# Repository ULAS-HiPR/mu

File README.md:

# Mu

Mu is a standalone SiPM/scintillator cosmic-ray detector and flight logger developed alongside the [Ogma avionics stack](https://sean-osullivan.com/projects/ogma/). It is designed to fly as its own black box: battery power in, particle and pressure data logged to onboard flash, then post-flight readout.

> [!CAUTION]
> **Rev 1 assembly corrections:** The `MICROFC-60035-SMT-TR1` SiPM footprint nets are reversed. On an existing Rev 1 PCB, mount U3 180 degrees from the orientation indicated by the footprint's pin-1 marker. This puts SiPM pin 3 (cathode) on PCB pad 1, the filtered HV-bias node, and SiPM pin 1 (anode) on PCB pad 3, the U5 inverting-input node. Pins 2 (fast output) and 4 (no connect) then exchange two unused PCB pads.
>
> The Rev 1 footprint also connects centre pad 5 to AGND. [Onsemi specifies pin 5 as no connect and recommends leaving the paddle unsoldered and floating](https://www.onsemi.com/download/data-sheet/pdf/microc-series-d.pdf). On the working board, a tiny piece of Blu Tack on the PCB beneath pad 5 kept the centre paddle off the board, and the sensor was attached to four small solder balls around the outer pads. A new PCB revision should correct the pin 1/pin 3 net mapping and leave pad 5 floating instead of relying on either assembly workaround.

## Hardware

- 50 x 50 x 20 mm BC-408 plastic scintillator.
- Onsemi MicroFC-60035 6 x 6 mm SiPM biased at about 30 V.
- OPA656/OPA814-class transimpedance readout around a 2.5 V reference.
- STM32F042 controller, W25Q128 external flash, and MS5607 barometer.
- Optional CAN interface; standalone logging does not depend on the Ogma stack.

## Repository

- `mu.kicad_sch`, `power.kicad_sch`, and `mu.kicad_pcb` - KiCad hardware design.
- `fabrication/` - Rev 1 manufacturing outputs.
- `Lib/` - project symbols, footprints, and 3D models.
- `SiPM Test Samples/` - raw oscilloscope samples.

Firmware, the field dashboard, and current flight preparation are on [`mu/f042-bringup`](https://github.com/ULAS-HiPR/mu/tree/mu/f042-bringup).

## Status

Mu has detected and logged real particle pulses on the bench and flew at Mach26, but it did not record a clean in-flight particle run. The reproduced fault is mechanical over-compression of the scintillator/SiPM stack. Packaging and flight validation remain in progress; Mu is not yet flight-proven.

## Manufacturing support

Rev 1 PCB fabrication was sponsored through [EasyEDA Education](https://easyeda.com/education) and manufactured by [JLCPCB](https://jlcpcb.com/). The board was designed in KiCad and imported into EasyEDA Pro for the sponsorship and manufacturing workflow.

## More information

See the [Mu project write-up](https://sean-osullivan.com/projects/mu/) for the detector, bring-up failures, pulse captures, and flight diagnosis.

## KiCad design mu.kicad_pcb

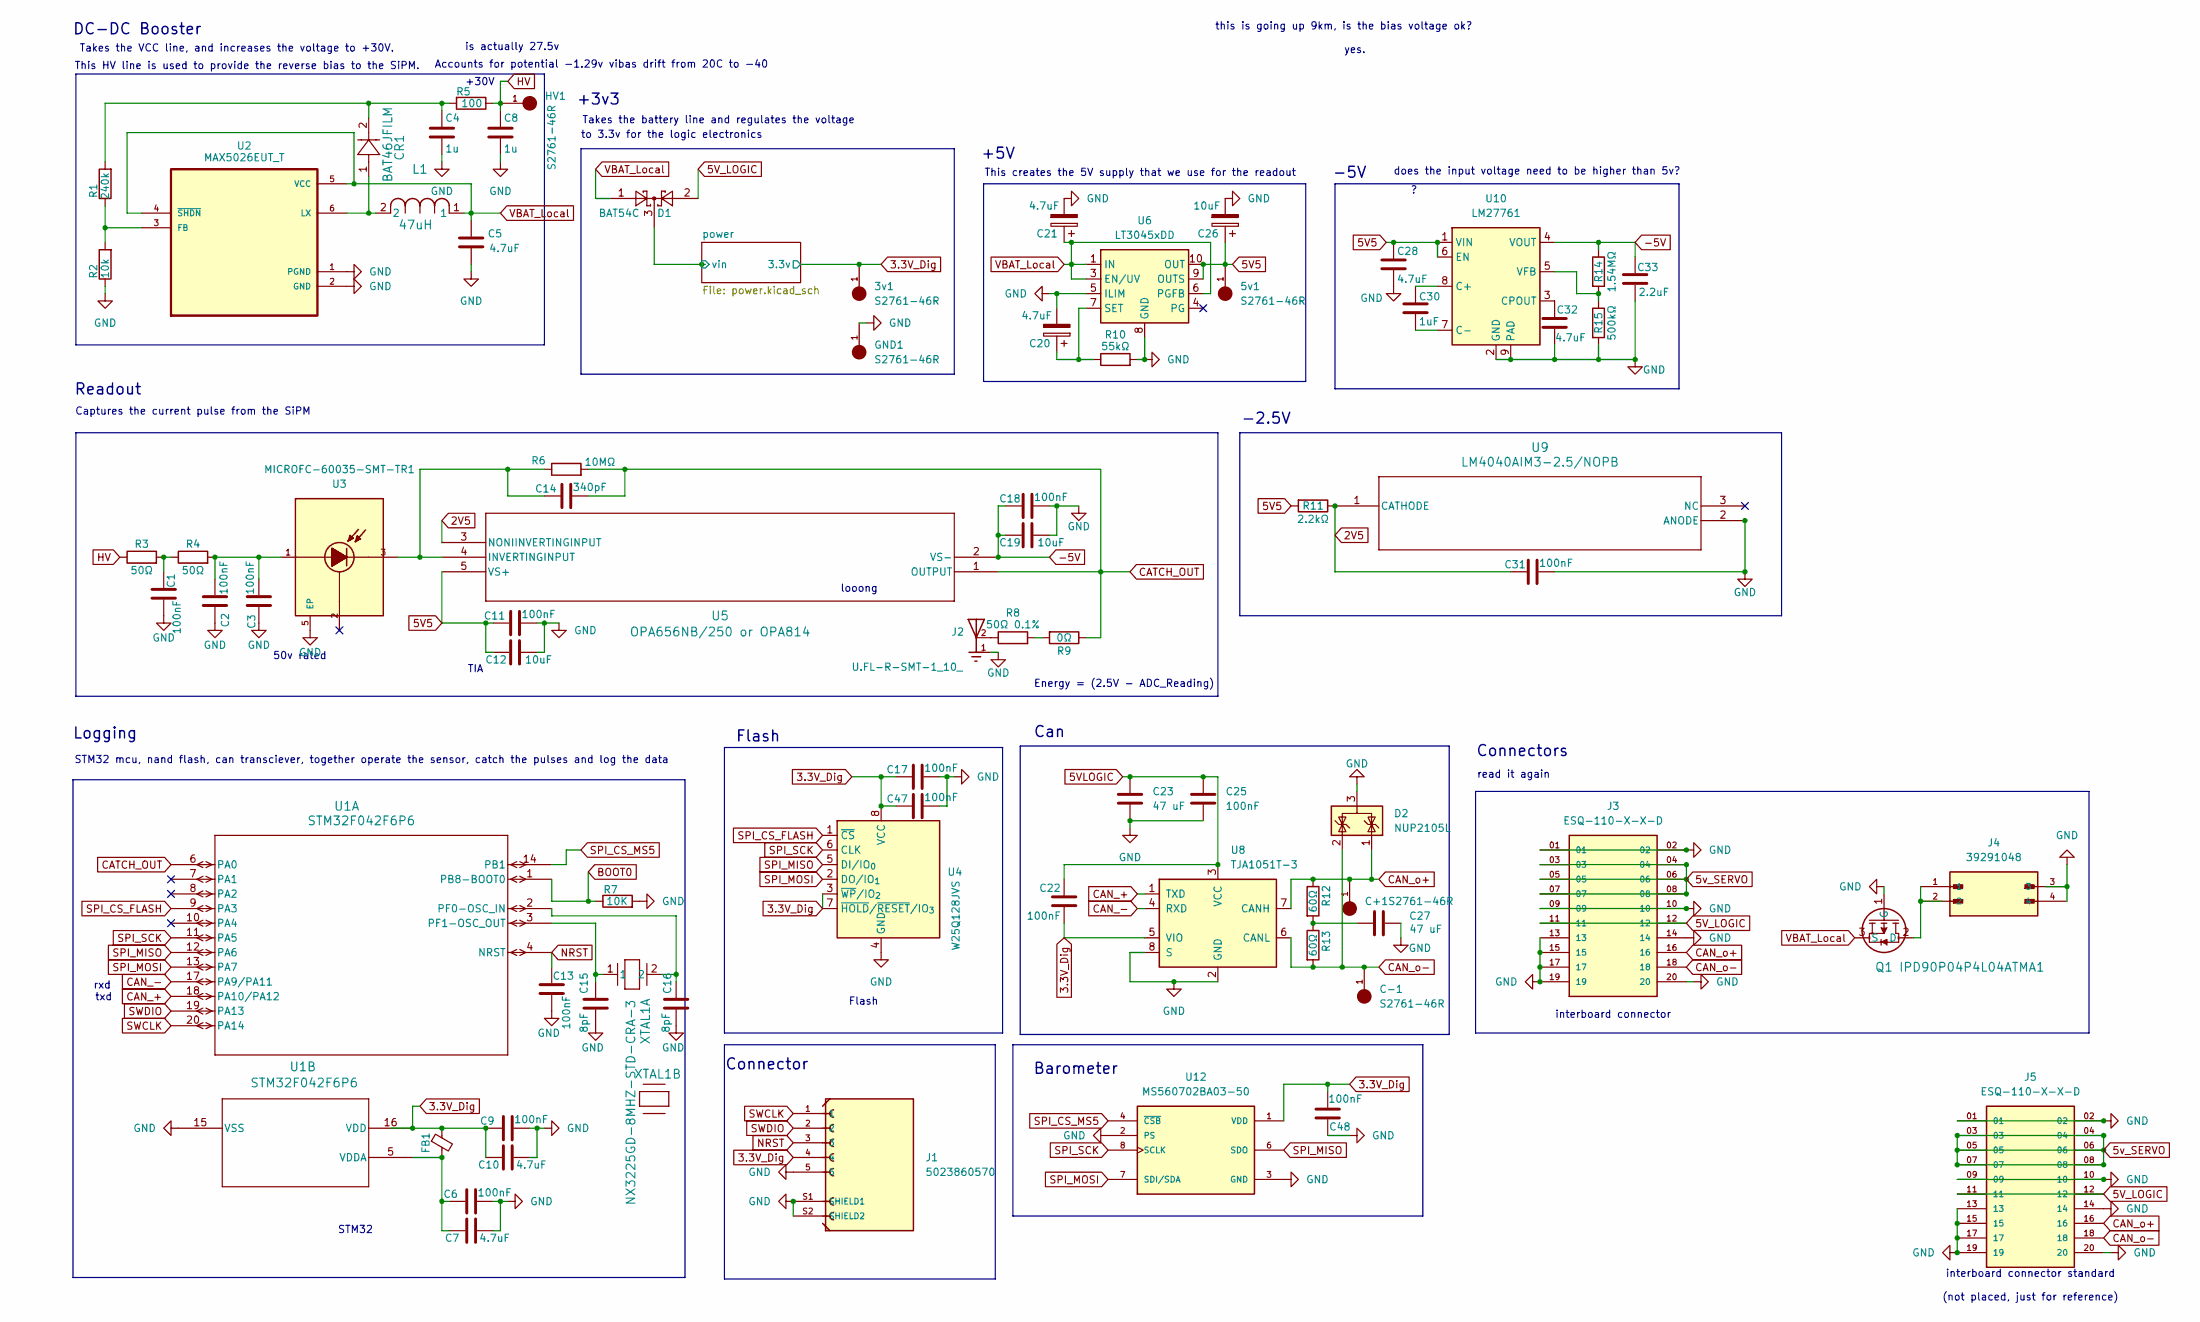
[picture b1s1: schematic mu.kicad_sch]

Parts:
3v1, 5v1: S2761-46R; HARWIN_S2761-46R; PARTREV 1
C1, C2, C3, C6, C9, C11, C13, C17, C18, C22, C25, C31, C47: 100nF; C_0402_1005Metric
C4, C8: 1u; R_0402_1005Metric
C5, C28, C32: 4.7uF; R_0402_1005Metric
C7, C10, C20, C21: 4.7uF; C_0402_1005Metric
C12: 10uF; C_0402_1005Metric
C14: 340pF; C_0402_1005Metric
C15, C16: 8pF; C_0402_1005Metric
C19, C26: 10uF; C_0603_1608Metric
C23, C27: 47 uF; C_0603_1608Metric
C30: 1uF; R_0402_1005Metric
C33: 2.2uF; C_0603_1608Metric
C48: 100nF; R_0402_1005Metric
C+1: S2761-46R; HARWIN_S2761-46R; PARTREV 1
C-1: S2761-46R; HARWIN_S2761-46R; PARTREV 1
CR1: BAT46JFILM; SOD-323_STM
D1: BAT54C; SOT-23
D2: NUP2105L; SOT-23
FB1: ferrite; L_0402_1005Metric
GND1: S2761-46R; HARWIN_S2761-46R; PARTREV 1
HV1: S2761-46R; HARWIN_S2761-46R; PARTREV 1
J1: 5023860570; MOLEX_5023860570; PARTREV F
J2: U.FL-R-SMT-1_10_; HRS_U.FL-R-SMT-1_10_
J3, J5: ESQ-110-X-X-D; SAMTEC_ESQ-110-14-G-D; PARTREV NA
J4: 39291048; MOLEX_39291048; PARTREV N1
L1: 47uH; IND_BOURNS_SRN4018
Q1: IPD90P04P4L04ATMA1; PG-TO252-3-313_INF-L
R1: 240k; R_0402_1005Metric
R2: 10k; R_0402_1005Metric
R3, R4: 50Ω; R_0402_1005Metric
R5: 100; R_0402_1005Metric
R6: 10MΩ; R_0402_1005Metric
R7: 10K; R_0402_1005Metric
R8: 50Ω 0.1%; R_0402_1005Metric
R9: 0Ω; R_0402_1005Metric
R10: 55kΩ; R_0402_1005Metric
R11: 2.2kΩ; R_0402_1005Metric
R12, R13: 60Ω; R_0402_1005Metric
R14: 1.54MΩ; R_0402_1005Metric
R15: 500kΩ; R_0402_1005Metric
U1: STM32F042F6P6; TSSOP20
U2: MAX5026EUT_T; SOT95P280X145-6N
U3: MICROFC-60035-SMT-TR1; XDCR_MICROFC-60035-SMT-TR1; PARTREV 31 JUL 2018
U4: W25Q128JVS; SOIC-8_5.3x5.3mm_P1.27mm
U5: OPA656NB/250 or OPA814; DBV5
U6: LT3045xDD; DFN-10-1EP_3x3mm_P0.5mm_EP1.65x2.38mm
U8: TJA1051T-3; SOIC-8_3.9x4.9mm_P1.27mm
U9: LM4040AIM3-2.5/NOPB; DBZ3
U10: LM27761; WSON-8-1EP_2x2mm_P0.5mm_EP0.9x1.6mm
U12: MS560702BA03-50; SON125P300X500X100-8N
XTAL1: NX3225GD-8MHZ-STD-CRA-3; XTAL_NX3225GD-8MHZ-STD-CRA-3_NDK

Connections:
2V5: C31.1, R11.1, U5.3 (NONIINVERTINGINPUT), U9.1 (CATHODE)
3.3V_Dig: 3v1.1, C9.1, C10.1, C17.1, C22.1, C47.1, C48.2, FB1.1, J1.4, U1.16 (VDD), U4.3 (~WP/IO_{2}), U4.7 (~HOLD/~RESET/IO_{3}), U4.8 (VCC), U8.5 (VIO), U12.1 (VDD); also elsewhere on the board
5V5: 5v1.1, C11.1, C12.1, C26.1, C28.1, R11.2, U5.5 (VS+), U6.9 (OUTS), U6.10 (OUT), U10.1 (VIN), U10.6 (EN); also elsewhere on the board
5VLOGIC: C22.2, C23.1, C25.1, U8.3 (VCC)
5V_LOGIC: D1.2, J3.11, J3.12, J5.11, J5.12
5v_SERVO: J3.03, J3.04, J3.05, J3.06, J3.07, J3.08, J5.03, J5.04, J5.05, J5.06, J5.07, J5.08
-5V: C18.1, C19.1, C33.1, R14.1, U5.2 (VS-), U10.4 (VOUT)
/power/vin: D1.3; also elsewhere on the board
AGND: C1.2, C2.2, C3.1, C4.2, C5.2, C6.2, C7.2, C8.2, C9.2, C10.2, C11.2, C12.2, C13.2, C15.1, C16.2, C17.2, C18.2, C19.2, C20.2, C21.2, C23.2, C25.2, C26.2, C27.2, C28.2, C31.2, C32.2, C33.2, C47.2, C48.1, D2.3 (A), GND1.1, J1.5, J1.S1 (SHIELD1), J1.S2 (SHIELD2), J2.1, J2.3, J3.01, J3.02, J3.09, J3.10, J3.13, J3.14, J3.15, J3.17, J3.19, J3.20, J4.3, J4.4, J5.01, J5.02, J5.09, J5.10, J5.13, J5.14, J5.15, J5.17, J5.19, J5.20, Q1.1 (G), R2.1, R7.2, R10.2, R15.2, U1.15 (VSS), U2.1 (PGND), U2.2 (GND), U3.5 (EP), U4.4 (GND), U6.5 (ILIM), U6.8 (GND), U6.11 (GND), U8.2 (GND), U8.8 (S), U9.2 (ANODE), U10.2 (GND), U10.9 (PAD), U12.2 (PS), U12.3 (GND); also elsewhere on the board
BOOT0: R7.1, U1.1 (PB8-BOOT0)
CAN_+: U1.18 (PA10/PA12), U8.1 (TXD)
CAN_-: U1.17 (PA9/PA11), U8.4 (RXD)
CAN_o+: C+1.1, D2.1 (K), J3.16, J5.16, R12.1, U8.7 (CANH); also elsewhere on the board
CAN_o-: C-1.1, D2.2 (K), J3.18, J5.18, R13.2, U8.6 (CANL); also elsewhere on the board
CATCH_OUT: C14.2, R6.2, R9.1, U1.6 (PA0), U5.1 (OUTPUT)
HV: C8.1, HV1.1, R3.1, R5.1; also elsewhere on the board
NRST: C13.1, J1.3, U1.4 (NRST)
unnamed: C1.1, R3.2, R4.1
unnamed: C2.1, C3.2, R4.2, U3.1
unnamed: C4.1, CR1.2, R1.2, R5.2
unnamed: C27.1, R12.2, R13.1
unnamed: J2.2, R8.1
unnamed: J4.1, J4.2, Q1.2 (D)
unnamed: R8.2, R9.2
unnamed: C16.1, U1.2 (PF0-OSC_IN), XTAL1.2
unnamed: C15.2, U1.3 (PF1-OSC_OUT), XTAL1.1
unnamed: C6.1, C7.1, FB1.2, U1.5 (VDDA)
unnamed: R1.1, R2.2, U2.3 (FB)
unnamed: CR1.1, L1.2, U2.6 (LX)
unnamed: C14.1, R6.1, U3.3, U5.4 (INVERTINGINPUT)
unnamed: C20.1, R10.1, U6.7 (SET)
unnamed: C30.1, U10.8 (C+)
unnamed: C30.2, U10.7 (C-)
unnamed: C32.1, U10.3 (CPOUT)
unnamed: R14.2, R15.1, U10.5 (VFB)
SPI_CS_FLASH: U1.9 (PA3), U4.1 (~CS)
SPI_CS_MS5: U1.14 (PB1), U12.4 (~CSB), U12.5 (~CSB)
SPI_MISO: U1.12 (PA6), U4.5 (DI/IO_{0}), U12.6 (SDO)
SPI_MOSI: U1.13 (PA7), U4.2 (DO/IO_{1}), U12.7 (SDI/SDA)
SPI_SCK: U1.11 (PA5), U4.6 (CLK), U12.8 (SCLK)
SWCLK: J1.1, U1.20 (PA14)
SWDIO: J1.2, U1.19 (PA13)
VBAT_Local: C5.1, C21.1, D1.1, L1.1, Q1.3 (S), U2.4 (~SHDN), U2.5 (VCC), U6.1 (IN), U6.2 (IN), U6.3 (EN/UV), U6.6 (PGFB)

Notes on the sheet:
Takes the battery line and regulates the voltage
looong
rxd
read it again
txd
TIA
Barometer
-5V
interboard connector
DC-DC Booster
-2.5V
Flash
does the input voltage need to be higher than 5v?
interboard connector standard (not placed, just for reference)
STM32 mcu, nand flash, can transciever, together operate the sensor, catch the pulses and log the data
Logging
50v rated
Flash
+3v3
this is going up 9km, is the bias voltage ok? yes.
Readout
This HV line is used to provide the reverse bias to the SiPM.
Takes the VCC line, and increases the voltage to +30V.
This creates the 5V supply that we use for the readout
Connector
is actually 27.5v
Can
+5V
to 3.3v for the logic electronics
Captures the current pulse from the SiPM
Accounts for potential -1.29v vibas drift from 20C to -40
+30V
Connectors
Energy = (2.5V - ADC_Reading)
STM32

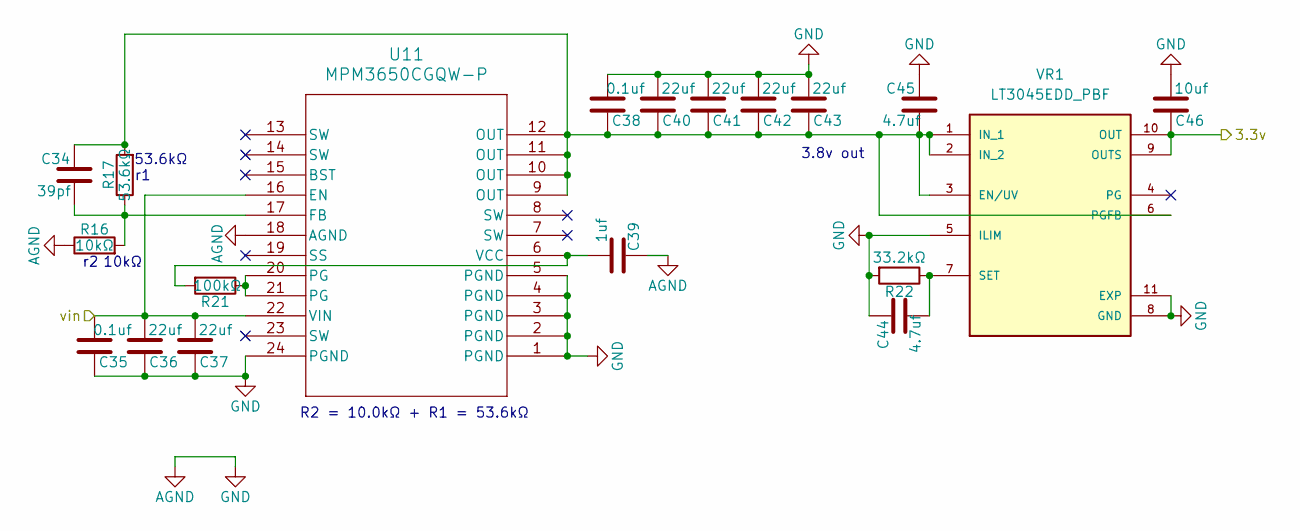
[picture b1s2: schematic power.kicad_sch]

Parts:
C34: 39pf; C_0402_1005Metric
C35, C38: 0.1uf; C_0402_1005Metric
C36, C37, C40, C41, C42, C43: 22uf; C_0603_1608Metric
C39: 1uf; C_0402_1005Metric
C44, C45: 4.7uf; C_0402_1005Metric
C46: 10uf; C_0603_1608Metric
R16: 10kΩ; R_0402_1005Metric
R17: 53.6kΩ; R_0402_1005Metric
R21: 100kΩ; R_0402_1005Metric
R22: 33.2kΩ; R_0402_1005Metric
U11: MPM3650CGQW-P; QFN-24_MPM3650_MNP
VR1: LT3045EDD_PBF; SON50P300X300X80-11N; PARTREV C

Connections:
3.3V_Dig: C46.1, VR1.9 (OUTS), VR1.10 (OUT); also elsewhere on the board
/power/vin: C35.2, C36.2, C37.2, U11.16 (EN), U11.22 (VIN); also elsewhere on the board
AGND: C35.1, C36.1, C37.1, C38.2, C39.1, C40.2, C41.2, C42.2, C43.2, C44.1, C45.1, C46.2, R16.1, R22.2, U11.1 (PGND), U11.2 (PGND), U11.3 (PGND), U11.4 (PGND), U11.5 (PGND), U11.18 (AGND), U11.24 (PGND), VR1.5 (ILIM), VR1.8 (GND), VR1.11 (EXP); also elsewhere on the board
unnamed: R21.1, U11.20 (PG), U11.21 (PG)
unnamed: C34.2, R16.2, R17.1, U11.17 (FB)
unnamed: C39.2, R21.2, U11.6 (VCC)
unnamed: C34.1, C38.1, C40.1, C41.1, C42.1, C43.1, C45.2, R17.2, U11.9 (OUT), U11.10 (OUT), U11.11 (OUT), U11.12 (OUT), VR1.1 (IN_1), VR1.2 (IN_2), VR1.3 (EN/UV), VR1.6 (PGFB)
unnamed: C44.2, R22.1, VR1.7 (SET)

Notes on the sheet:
10kΩ
53.6kΩ
R2 = 10.0kΩ + R1 = 53.6kΩ
3.8v out

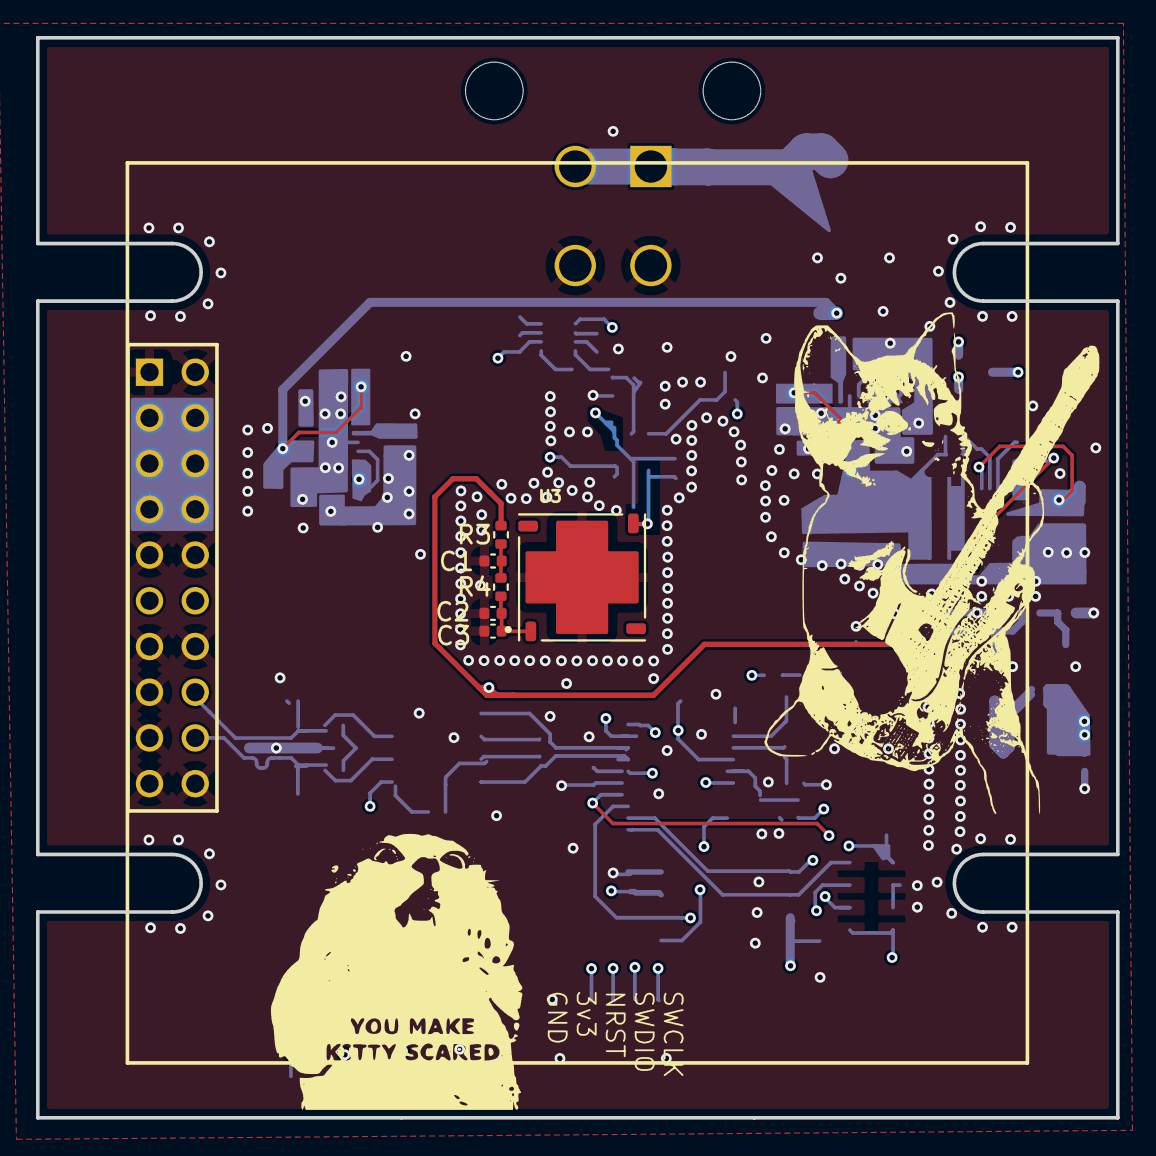
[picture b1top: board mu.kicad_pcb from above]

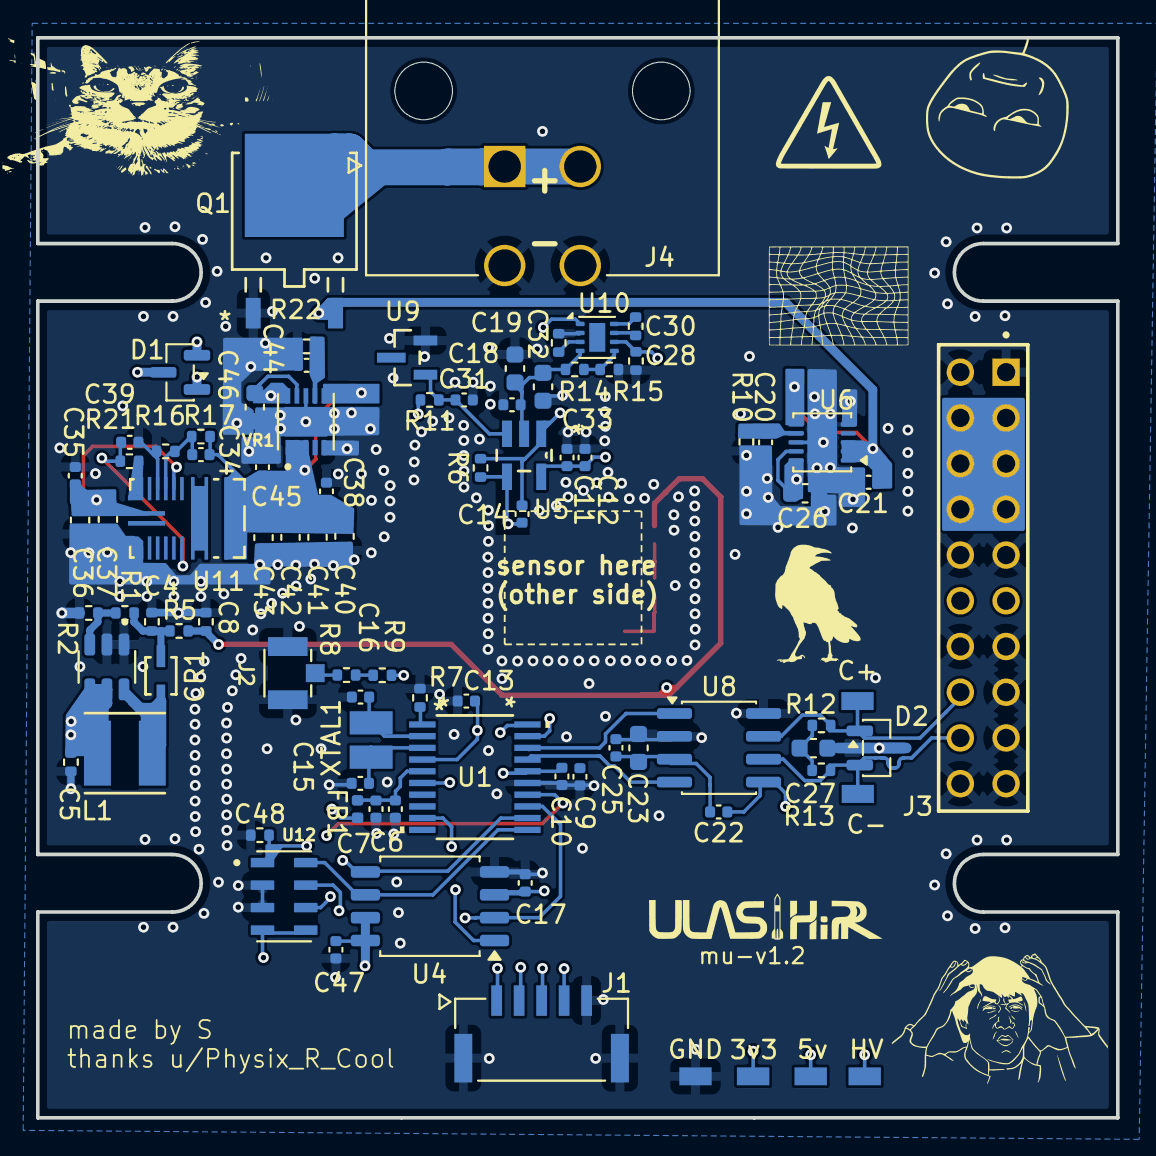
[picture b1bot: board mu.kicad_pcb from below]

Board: 6 copper layers, 60.0 x 60.0 mm, 94 parts (88 on the bottom side), 48 nets.

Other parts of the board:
3v3, 5v: S2761-46R; HARWIN_S2761-46R
C+: S2761-46R; HARWIN_S2761-46R
C-: S2761-46R; HARWIN_S2761-46R
GND: S2761-46R; HARWIN_S2761-46R
HV: S2761-46R; HARWIN_S2761-46R

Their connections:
3.3V_Dig: 3v3.1; also elsewhere on the board
5V5: 5v.1; also elsewhere on the board
AGND: GND.1; also elsewhere on the board
CAN_o+: C+.1; also elsewhere on the board
CAN_o-: C-.1; also elsewhere on the board
HV: HV.1; also elsewhere on the board

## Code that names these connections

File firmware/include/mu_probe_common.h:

#ifndef MU_PROBE_COMMON_H
#define MU_PROBE_COMMON_H

#include "stm32f0xx.h"

#include <cstdint>

namespace mu {

constexpr std::uint32_t kSystemClockHz = 48000000UL;
constexpr std::uint32_t kTimerTickHz = 1000000UL;

constexpr std::uint8_t kCatchOutAdcIndex = 0U;  // PA0
constexpr std::uint8_t kFlashCsIndex = 3U;      // PA3
constexpr std::uint8_t kSpiSckIndex = 5U;       // PA5
constexpr std::uint8_t kSpiMisoIndex = 6U;      // PA6
constexpr std::uint8_t kSpiMosiIndex = 7U;      // PA7
constexpr std::uint8_t kCanRxIndex = 11U;       // PA11
constexpr std::uint8_t kCanTxIndex = 12U;       // PA12
constexpr std::uint8_t kMs5607CsIndex = 1U;     // PB1

constexpr std::uint16_t kCatchOutAdcPin = 1U << kCatchOutAdcIndex;
constexpr std::uint16_t kFlashCsPin = 1U << kFlashCsIndex;
constexpr std::uint16_t kSpiSckPin = 1U << kSpiSckIndex;
constexpr std::uint16_t kSpiMisoPin = 1U << kSpiMisoIndex;
constexpr std::uint16_t kSpiMosiPin = 1U << kSpiMosiIndex;
constexpr std::uint16_t kCanRxPin = 1U << kCanRxIndex;
constexpr std::uint16_t kCanTxPin = 1U << kCanTxIndex;
constexpr std::uint16_t kMs5607CsPin = 1U << kMs5607CsIndex;

enum class SpiWireMode : std::uint8_t {
    Normal = 0U,   // MCU PA7 -> peripheral SDI, peripheral SDO -> MCU PA6.
    Swapped = 1U,  // MCU PA6 -> peripheral DI, peripheral DO -> MCU PA7.
};

enum class SpiClockMode : std::uint8_t {
    Mode0 = 0U,
    Mode3 = 3U,
};

inline void enable_gpio_clocks()
{
    RCC->AHBENR |= RCC_AHBENR_GPIOAEN | RCC_AHBENR_GPIOBEN;
    (void)RCC->AHBENR;
}

inline void set_pin_high(GPIO_TypeDef* port, std::uint16_t pin)
{
    port->BSRR = pin;
}

inline void set_pin_low(GPIO_TypeDef* port, std::uint16_t pin)
{
    port->BRR = pin;
}

inline void configure_input(GPIO_TypeDef* port, std::uint8_t index)
{
    const std::uint32_t shift = static_cast<std::uint32_t>(index) * 2UL;
    port->MODER &= ~(3UL << shift);
    port->PUPDR &= ~(3UL << shift);
}

inline void configure_output(GPIO_TypeDef* port, std::uint8_t index)
{
    const std::uint32_t shift = static_cast<std::uint32_t>(index) * 2UL;
    port->MODER = (port->MODER & ~(3UL << shift)) | (1UL << shift);
    port->OTYPER &= ~(1UL << index);
    port->PUPDR &= ~(3UL << shift);
    port->OSPEEDR |= (3UL << shift);
}

inline void configure_analog(GPIO_TypeDef* port, std::uint8_t index)
{
    const std::uint32_t shift = static_cast<std::uint32_t>(index) * 2UL;
    port->MODER |= (3UL << shift);
    port->PUPDR &= ~(3UL << shift);
}

inline void configure_alternate(GPIO_TypeDef* port, std::uint8_t index, std::uint8_t af)
{
    const std::uint32_t shift = static_cast<std::uint32_t>(index) * 2UL;
    port->MODER = (port->MODER & ~(3UL << shift)) | (2UL << shift);
    port->OTYPER &= ~(1UL << index);
    port->PUPDR &= ~(3UL << shift);
    port->OSPEEDR |= (3UL << shift);

    const std::uint8_t afr_index = index < 8U ? 0U : 1U;
    const std::uint8_t afr_shift = static_cast<std::uint8_t>((index & 7U) * 4U);
    port->AFR[afr_index] =
        (port->AFR[afr_index] & ~(0xFUL << afr_shift)) |
        (static_cast<std::uint32_t>(af) << afr_shift);
}

inline void clock_init_hsi48()
{
    RCC->CR2 |= RCC_CR2_HSI48ON;
    while ((RCC->CR2 & RCC_CR2_HSI48RDY) == 0U) {}

    FLASH->ACR |= FLASH_ACR_LATENCY;

    RCC->CFGR &= ~RCC_CFGR_SW;
    RCC->CFGR |= RCC_CFGR_SW_HSI48;
    while ((RCC->CFGR & RCC_CFGR_SWS) != RCC_CFGR_SWS_HSI48) {}

    SystemCoreClock = kSystemClockHz;
}

inline void systick_init_1khz()
{
    SysTick_Config(kSystemClockHz / 1000UL);
    NVIC_SetPriority(SysTick_IRQn, 0U);
}

inline void timebase_init()
{
    RCC->APB1ENR |= RCC_APB1ENR_TIM3EN;
    (void)RCC->APB1ENR;

    TIM3->PSC = (kSystemClockHz / kTimerTickHz) - 1UL;
    TIM3->ARR = 0xFFFFU;
    TIM3->EGR = TIM_EGR_UG;
    TIM3->CR1 = TIM_CR1_CEN;
}

inline void delay_us(std::uint32_t us)
{
    while (us > 0U) {
        const std::uint32_t chunk = us > 60000U ? 60000U : us;
        TIM3->CNT = 0U;
        while (TIM3->CNT < chunk) {}
        us -= chunk;
    }
}

inline void delay_ms(std::uint32_t ms)
{
    while (ms-- > 0U) {
        delay_us(1000U);
    }
}

inline void configure_safe_chip_selects()
{
    enable_gpio_clocks();
    configure_output(GPIOA, kFlashCsIndex);
    configure_output(GPIOB, kMs5607CsIndex);
    set_pin_high(GPIOA, kFlashCsPin);
    set_pin_high(GPIOB, kMs5607CsPin);
}

} // namespace mu

#endif // MU_PROBE_COMMON_H

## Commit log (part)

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2025-12-14 first
2025-12-14 imported first component
2025-12-14 progress
2025-12-17 big progress, superfluous caps added
2025-12-17 sent v1 to stephen
2025-12-17 push before fabien
2025-12-24 huge progress, caught issue
2025-12-24 clean
2025-12-25 nearly ready for layout
2025-12-26 svgs for readmes
2025-12-28 added usb c and fixed many silly issues
2025-12-28 flipflop is 3v3
2025-12-28 esd protection
2025-12-28 schematic locked in, connenctors added
2025-12-29 ready to place
2026-01-06 layout rocking
2026-01-11 organised
2026-01-12 progress2
2026-01-12 progress3
2026-01-14 nearly done now
2026-01-15 restructuring now that we've got the standard connector
2026-01-15 restructuring now that we've got the standard connector part 2
2026-01-15 routed
2026-01-15 route2
2026-01-15 routed fully, pending final checks
2026-01-15 ready for review
2026-01-15 programming stuff
2026-01-15 indeed
2026-01-16 ready to send off to stephen
2026-01-16 higher voltage diode
2026-01-19 ready to rock and roll
2026-01-21 refactored following thoughts
2026-01-21 huge
2026-01-21 huge2
2026-01-22 xt30 added
2026-01-22 spacer prints
2026-01-22 fixed the connector
2026-01-27 major revisions
2026-01-27 added the label
2026-01-30 minor cleaning
2026-01-30 drc pass
2026-01-30 thermal expansion vias
2026-01-31 cleanup readme
2026-01-31 Add additional logo image link to README
2026-02-03 3d model made
2026-02-05 refdes, test points, better connector
2026-02-05 power subschematic done
2026-02-06 overhaul
2026-02-06 cleaned some more
2026-02-09 lots done
2026-02-10 ready for upload
2026-02-25 ready for review the twost, nearly
2026-02-26 ready for review the twost, nearly, readout locked
2026-02-26 ready for review the twost, nearly, readout locked :)
2026-02-26 ready for review the twost, nearly, readout locked :), for real
2026-02-26 good to go
2026-02-27 ready to go, nearly
2026-03-01 ready 2 order
2026-03-31 hardware done
2026-06-28 Add Mu F042 bring-up firmware
